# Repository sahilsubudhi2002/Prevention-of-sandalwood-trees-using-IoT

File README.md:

# Prevention-of-sandalwood-trees-using-IoT

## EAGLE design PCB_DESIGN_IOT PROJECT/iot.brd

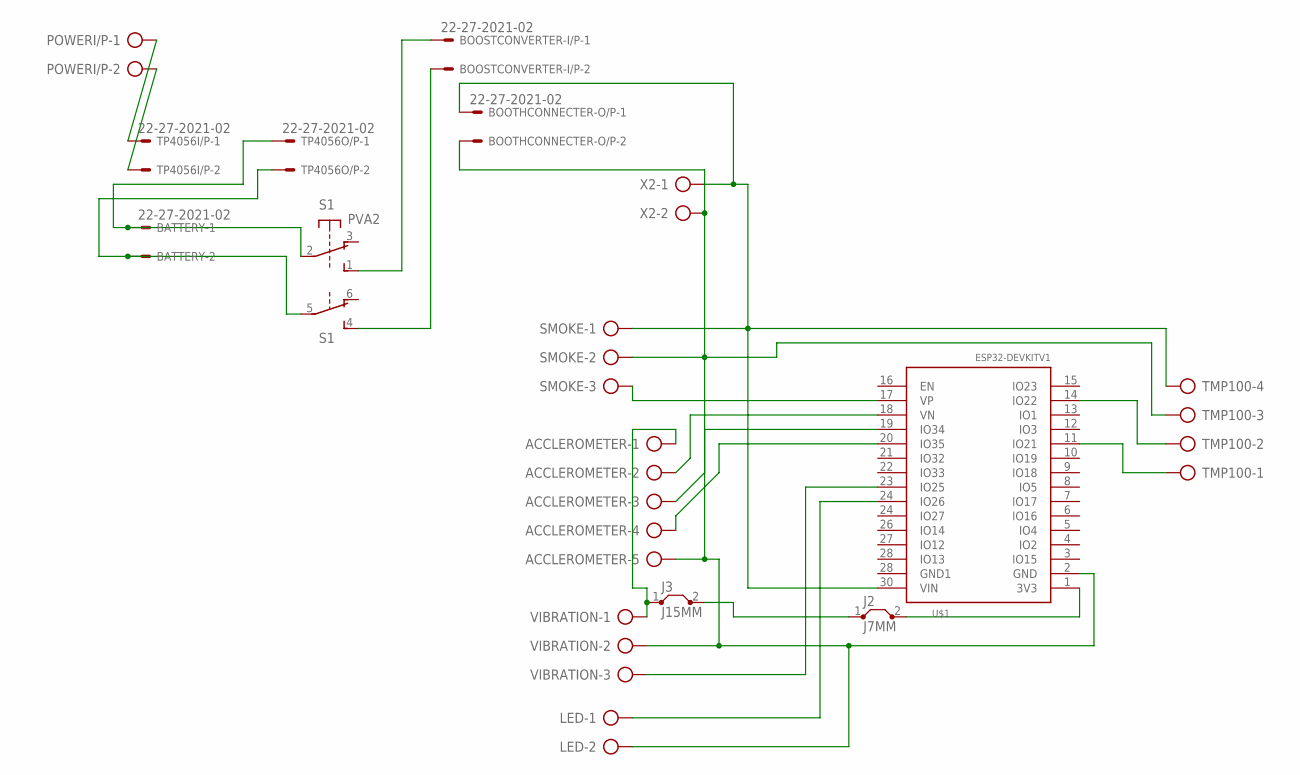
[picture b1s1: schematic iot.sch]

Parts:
ACCLEROMETER: AK500/5-H
BATTERY: 22-27-2021-02; 6410-02
BOOSTCONVERTER-I/P: 22-27-2021-02; 6410-02
BOOTHCONNECTER-O/P: 22-27-2021-02; 6410-02
J2: J7MM; 07
J3: J15MM; 15
LED: AK500/2-H
POWERI/P: AK500/2-H
S1: PVA2; PVA2F
SMOKE: AK500/3-H
TMP100: AK500/4-H
TP4056I/P, TP4056O/P: 22-27-2021-02; 6410-02
U$1: ESP32DEVKITV1; ESP32-DEVKITV1
VIBRATION: AK500/3-H
X2: AK500/2-H

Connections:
unnamed: ACCLEROMETER.2, U$1.18 (VN)
unnamed: ACCLEROMETER.3, U$1.19 (IO34)
unnamed: ACCLEROMETER.4, U$1.20 (IO35)
unnamed: SMOKE.3, U$1.17 (VP)
unnamed: U$1.23 (IO25), VIBRATION.3
unnamed: TMP100.2, U$1.14 (IO22)
unnamed: TMP100.1, U$1.11 (IO21)
unnamed: BOOTHCONNECTER-O/P.1, SMOKE.1, TMP100.4, U$1.30 (VIN), X2.1
unnamed: J2.1, J3.2
unnamed: ACCLEROMETER.1, J3.1, VIBRATION.1
unnamed: ACCLEROMETER.5, BOOTHCONNECTER-O/P.2, LED.2, SMOKE.2, TMP100.3, U$1.2 (GND), VIBRATION.2, X2.2
unnamed: LED.1, U$1.24 (IO27)
unnamed: POWERI/P.1, TP4056I/P.1
unnamed: POWERI/P.2, TP4056I/P.2
unnamed: BATTERY.1, S1.2, TP4056O/P.1
unnamed: BATTERY.2, S1.5, TP4056O/P.2
unnamed: BOOSTCONVERTER-I/P.1, S1.1 (S)
unnamed: BOOSTCONVERTER-I/P.2, S1.4 (S)
unnamed: J2.2, U$1.1 (3V3)

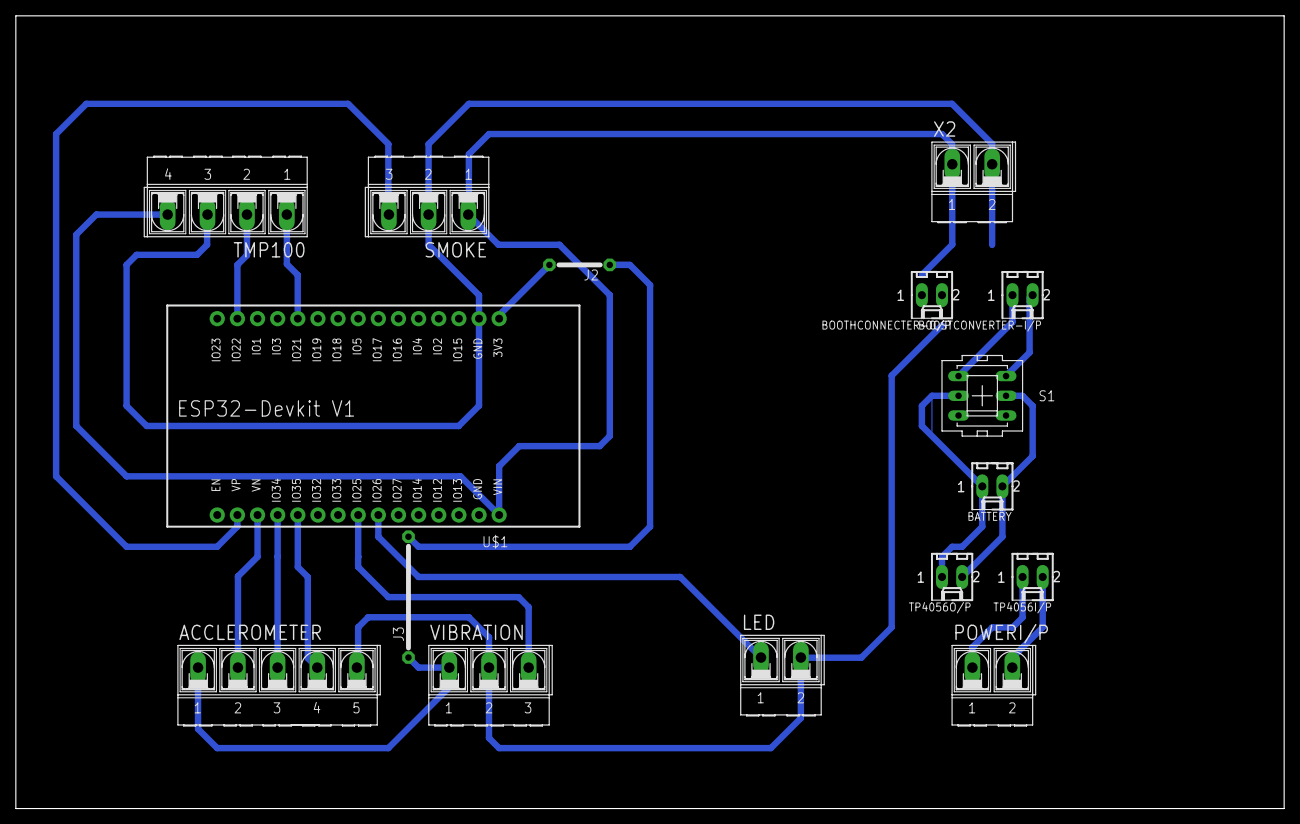
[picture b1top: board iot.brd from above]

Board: 2 copper layers, 160.0 x 100.0 mm, 16 parts (0 on the bottom side), 19 nets.
